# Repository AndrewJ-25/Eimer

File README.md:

# Eimer
Eimer is a wearable RP2040 devboard!

## Description and Features

A multi-axis accelerometer, 8 LEDs and 8 GPIO pads make Eimer an ideal wearable device. Solder pads are accompanied by holes to run the wire through, so there is no strain on the solder joint.

Eimer can be programmed using Arduino framework. Two mounting holes can be attached to a lanyard necklace, or safety pins.

Eimer can be powered with USB C or two CR2032 button cells (the board will work with one button cell, with a shorter battery life). Important note: do not plug in USB while cells are inserted!

I designed Eimer to get more comfortable with SMD and to learn more about MCUs. I started this project by following a tutorial posted in Hackclub Macondo before customising it.

The name comes from Irish mythology:)

## Assembly

All components can be soldered on a hotplate, except the coin cell holders which require hand-soldering.

## Schematic

## PCB

## BOM

|Designator                                                                              |Footprint                                  |Quantity|Description|Suggested source|Total cost, £|
|----------------------------------------------------------------------------------------|-------------------------------------------|--------|---------------------------|-----------|--|
|BT1, BT2                                                                                |BatteryHolder_Multicomp_BC-2001_1x2032     |2       |CR2032 cell holder|https://www.aliexpress.com/item/1005010097971513.html|2.00|
|C1, C10                                                                                 |0402                                       |2       |1uF capacitor|https://www.aliexpress.com/item/32435282135.html|0.67|
|C11, C12, C17, C2, C21, C3, C4, C5, C6, C7, C8, C9                                      |0402                                       |12      |0.1uF capacitor|https://www.aliexpress.com/item/32435282135.html|0.67
|C13, C14, C19, C20                                                                      |0603                                       |4       |10uF capacitor|https://www.aliexpress.com/item/1005007404529007.html|1.83|
|C15, C16                                                                                |0402                                       |2       |33pF capacitor|https://www.aliexpress.com/item/1005002960548572.html|1.27|
|D1, D2, D3, D4, D5, D6, D7, D8                                                          |0201                                       |8       |LED green|https://www.aliexpress.com/item/1005007406675682.html|5.05|
|J3                                                                                      |PinHeader_1x03_P2.54mm_Horizontal          |1       |1x3 horizontal pin header| https://www.aliexpress.com/item/1005007569841697.html|0.55|
|J4                                                                                      |USB_C_Receptacle_HRO_TYPE-C-31-M-12        |1       |USBC Receptacle|https://www.aliexpress.com/item/1005008805157100.html|1.04|
|L1                                                                                      |L_APV_ANR3015                              |1       |4.7uH inductor|https://www.aliexpress.com/item/1005001699576419.html|1.14|
|R1, R2                                                                                  |0402                                       |2       |5.1K resistor|https://www.aliexpress.com/item/4001321720241.html (multipack includes all required resistor values)|1.86|
|R10, R11, R12, R13, R14, R15, R16, R17, R5, R6                                          |0402                                       |10      |1k resistor|-|-|
|R18, R7                                                                                 |0402                                       |2       |10k resistor|-|-|
|R3, R4                                                                                  |0402                                       |2       |27ohm resistor|-|-|
|R8, R9                                                                                  |0402                                       |2       |4.7k resistor|-|-|
|RESET, RUN                                                                              |SW_Push_SPST_NO_Alps_SKRK                  |2       |Push switch|https://jlcpcb.com/partdetail/XUNPU-TS_1088AR02016/C720477|1.00|
|U1                                                                                      |QFN-56-1EP_7x7mm_P0.4mm_EP3.2x3.2mm        |1       |RP2040 MCU chip|https://www.aliexpress.com/item/1005007275652762.html|3.46|
|U2                                                                                      |SOT-23                                     |1       |MCP1700x-330xxTT voltage regulator|https://www.aliexpress.com/item/32808973510.html|0.99|
|U3                                                                                      |Texas_R-PDSO-G6                            |1       |TPS61221DCK boost converter|https://www.aliexpress.com/item/1005012857789997.html|3.69|
|U4                                                                                      |Winbond_USON-8-1EP_3x2mm_P0.5mm_EP0.2x1.6mm|1       |W25Q16JVUXIQ TR flash memory|https://www.aliexpress.com/item/1005012822339773.html|5.55|
|U5                                                                                      |LIS2DW12                                   |1       |LIS2DW12 accelerometer|https://www.aliexpress.com/item/1005009164629980.html|3.22|
|Y1                                                                                      |Crystal_SMD_3225-4Pin_3.2x2.5mm            |1       |12 MHz crystal|https://www.aliexpress.com/item/1005005409440787.html|2.50|
|PCB|-|1|PCB|https://jlcpcb.com/|2.95|
|Total| | | | |39.44|

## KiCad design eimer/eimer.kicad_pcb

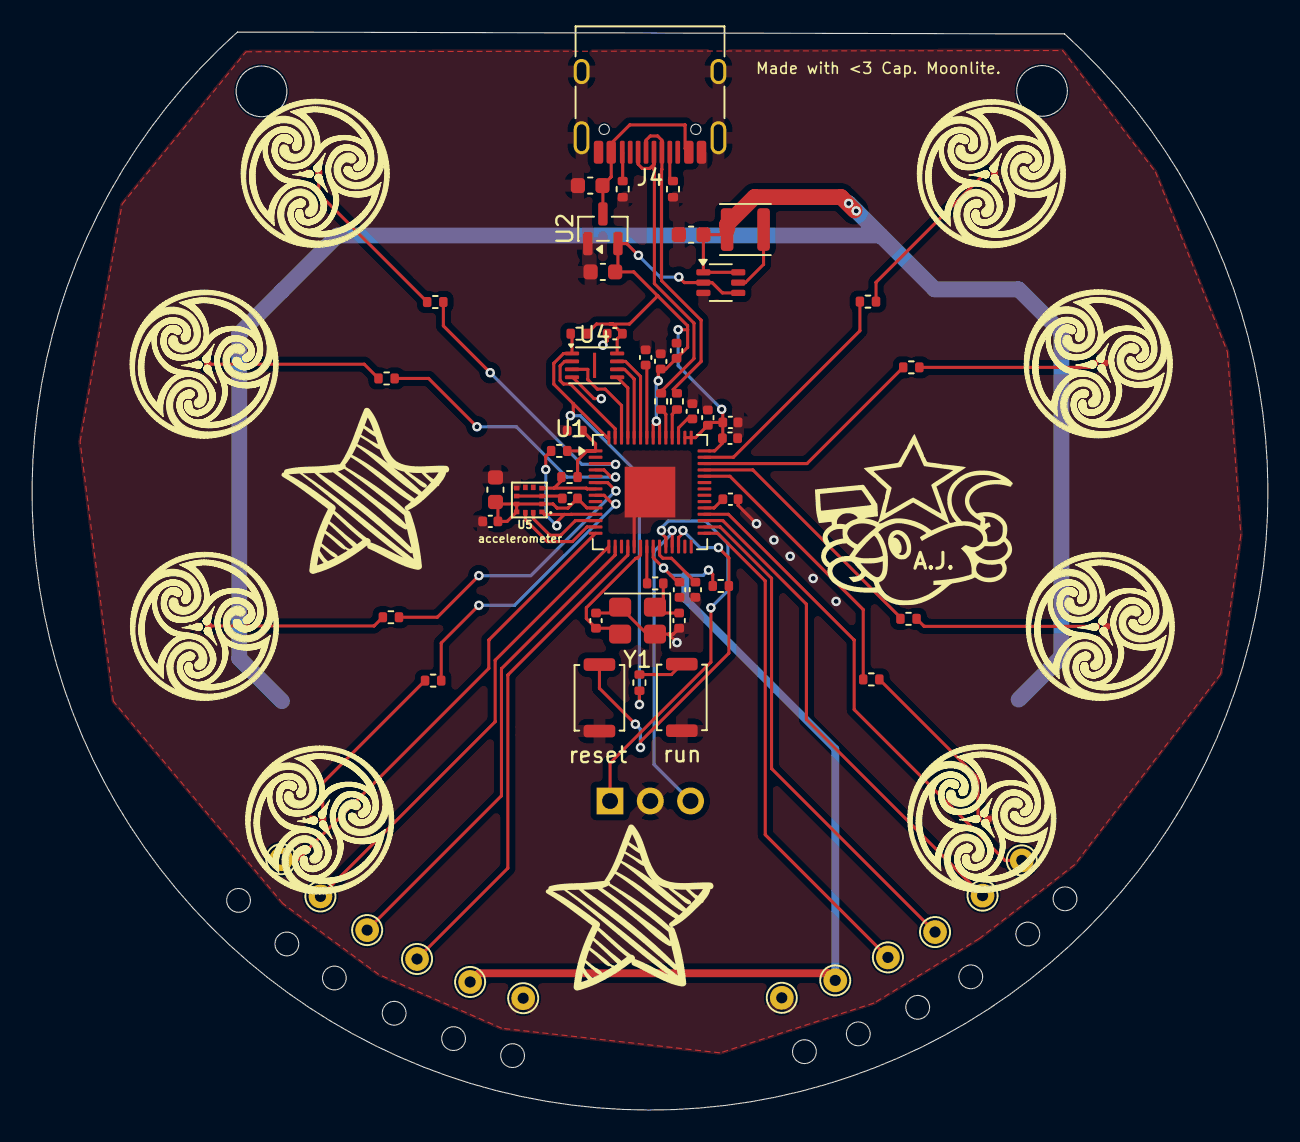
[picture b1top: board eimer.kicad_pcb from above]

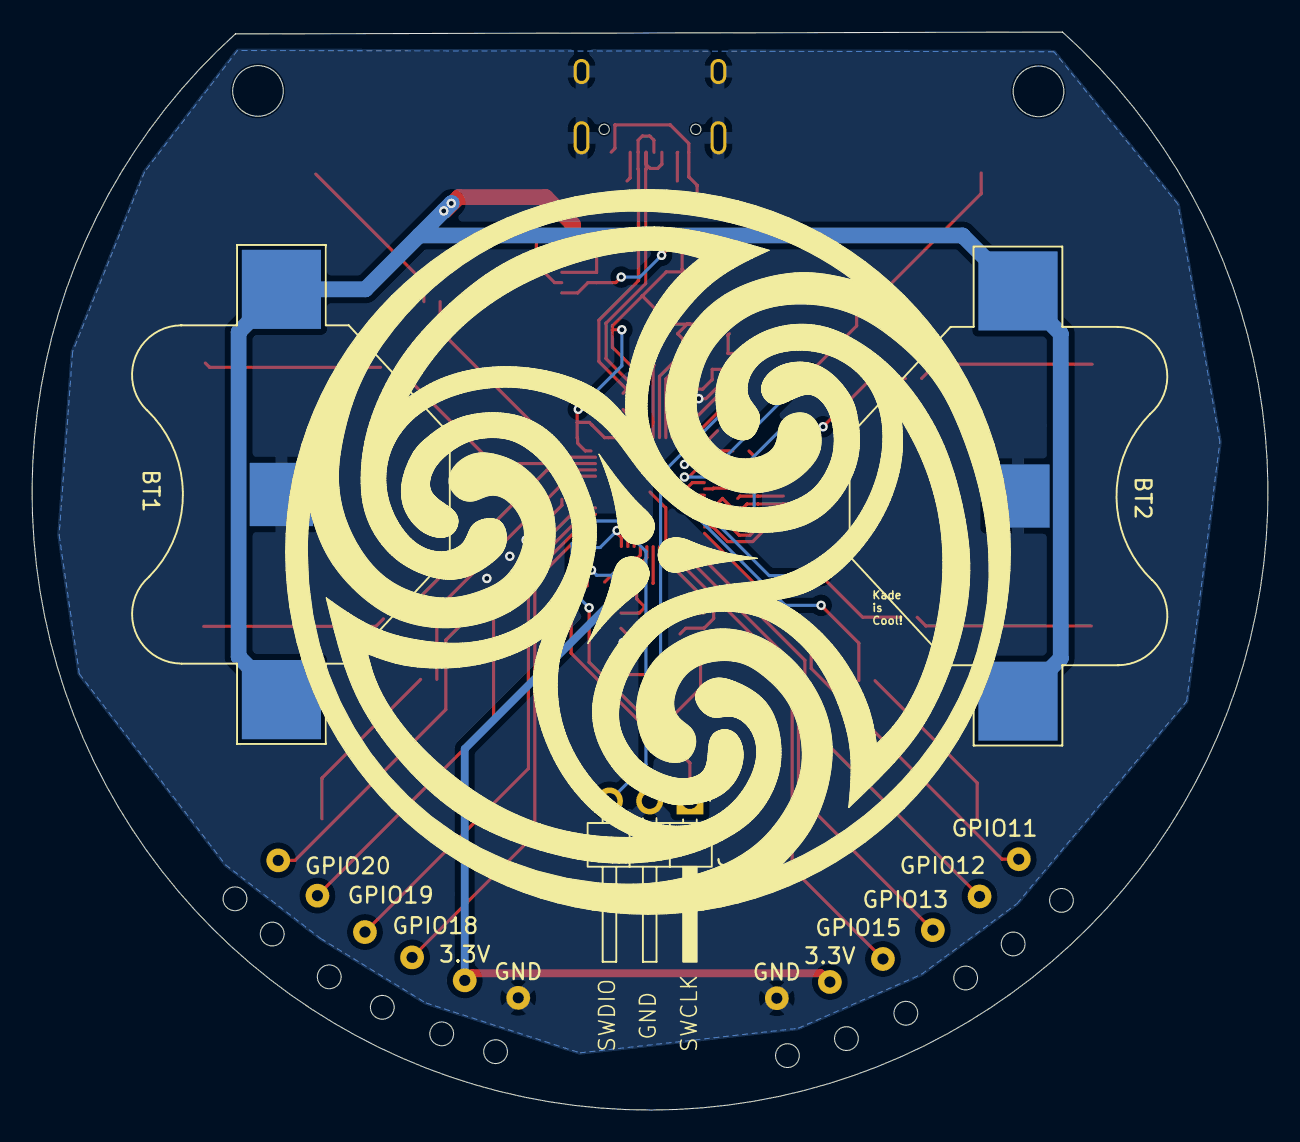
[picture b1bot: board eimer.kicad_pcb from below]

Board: 2 copper layers, 78.0 x 68.1 mm, 71 parts (3 on the bottom side), 53 nets.

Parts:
3.3V, 3.3V#2: TestPoint; TestPoint_THTPad_D1.5mm_Drill0.7mm
BT1, BT2: Battery_Cell; BatteryHolder_Multicomp_BC-2001_1x2032
C1, C10: 1uF; C_0402_1005Metric
C2, C3, C4, C5, C6, C7, C8, C9, C11, C12, C17, C21: 0.1uF; C_0402_1005Metric
C13, C14, C19, C20: 10uF; C_0603_1608Metric
C15, C16: 33pF; C_0402_1005Metric
D1, D2, D3, D4, D5, D6, D7, D8: LED; LED_0201_0603Metric
GND: TestPoint; TestPoint_THTPad_D1.5mm_Drill0.7mm
GND#2: TestPoint; TestPoint_THTPad_D1.5mm_Drill0.7mm
GPIO11, GPIO12, GPIO13, GPIO15, GPIO18, GPIO19, GPIO20, GPIO21: TestPoint; TestPoint_THTPad_D1.5mm_Drill0.7mm
J3: Conn_01x03; PinHeader_1x03_P2.54mm_Horizontal
J4: USB_C_Receptacle_USB2.0_14P; USB_C_Receptacle_HRO_TYPE-C-31-M-12
L1: 4.7uH; L_APV_ANR3015
R1, R2: 5.1K; R_0402_1005Metric
R3, R4: 27; R_0402_1005Metric
R5, R6: 1K; R_0402_1005Metric
R7: 10K; R_0402_1005Metric
R8, R9: 4.7k; R_0402_1005Metric
R10, R11, R12, R13, R14, R15, R16, R17: 1k; R_0402_1005Metric
R18: 10k; R_0402_1005Metric
U1: RP2040; QFN-56-1EP_7x7mm_P0.4mm_EP3.2x3.2mm
U2: MCP1700x-330xxTT; SOT-23
U3: TPS61221DCK; Texas_R-PDSO-G6
U4: W25Q16JVUXIQ TR; Winbond_USON-8-1EP_3x2mm_P0.5mm_EP0.2x1.6mm
U5: LIS2DW12; LIS2DS12
Y1: 12 MHz; Crystal_SMD_3225-4Pin_3.2x2.5mm
reset: SW_Push; SW_Push_SPST_NO_Alps_SKRK
run: SW_Push; SW_Push_SPST_NO_Alps_SKRK

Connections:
+1V1: C10.1, C11.1, C12.1, U1.23 (DVDD), U1.45 (VREG_VOUT), U1.50 (DVDD)
+3.3V: 3.3V.1 (1_1), 3.3V#2.1 (1_1), C1.1, C2.1, C3.1, C4.1, C5.1, C6.1, C7.1, C8.1, C9.1, C14.1, C17.1, C20.1, C21.1, R7.2, R8.1, R9.1, R18.1, U1.1 (IOVDD), U1.10 (IOVDD), U1.22 (IOVDD), U1.33 (IOVDD), U1.42 (IOVDD), U1.43 (ADC_AVDD), U1.44 (VREG_VIN), U1.48 (USB_VDD), U1.49 (IOVDD), U2.2 (VO), U3.2 (FB), U3.4 (VOUT), U4.8 (VCC), U5.2 (CS), U5.9 (VDD), U5.10 (VDD_IO)
GND: BT1.2 (-), BT2.2 (-), C1.2, C2.2, C3.2, C4.2, C5.2, C6.2, C7.2, C8.2, C9.2, C10.2, C11.2, C12.2, C13.2, C14.2, C15.1, C16.2, C17.2, C19.2, C20.2, C21.2, D1.1 (K), D2.1 (K), D3.1 (K), D4.1 (K), D5.1 (K), D6.1 (K), D7.1 (K), D8.1 (K), GND.1 (1_1), GND#2.1 (1_1), J3.2, J4.A1 (GND), J4.A12 (GND), J4.B1 (GND), J4.B12 (GND), J4.SH (SHIELD), R1.2, R2.1, U1.19 (TESTEN), U1.57 (GND), U2.1 (GND), U3.3 (GND), U4.4 (GND), U5.3 (SDO/SA0/MSDA), U5.6 (GND), U5.7 (RES), U5.8 (GND), Y1.2, Y1.4, reset.1, run.1
GPIO1: R10.2, U1.3 (GPIO1)
GPIO2: R11.2, U1.4 (GPIO2)
GPIO4: R12.2, U1.6 (GPIO4)
GPIO6: R13.2, U1.8 (GPIO6)
GPIO11: GPIO11.1 (1_1), U1.14 (GPIO11)
GPIO12: GPIO12.1 (1_1), U1.15 (GPIO12)
GPIO13: GPIO13.1 (1_1), U1.16 (GPIO13)
GPIO15: GPIO15.1 (1_1), U1.18 (GPIO15)
GPIO18: GPIO18.1 (1_1), U1.29 (GPIO18)
GPIO19: GPIO19.1 (1_1), U1.30 (GPIO19)
GPIO20: GPIO20.1 (1_1), U1.31 (GPIO20)
GPIO21: GPIO21.1 (1_1), U1.32 (GPIO21)
GPIO26/ADC0: R14.2, U1.38 (GPIO26/ADC0)
GPIO27/ADC1: R15.2, U1.39 (GPIO27/ADC1)
GPIO28/ADC2: R16.2, U1.40 (GPIO28/ADC2)
GPIO29/ADC3: R17.2, U1.41 (GPIO29/ADC3)
I2C_SCL: R8.2, U1.11 (GPIO8), U5.1 (SCL/SPC)
I2C_SDA: R9.2, U1.7 (GPIO5), U5.4 (SDA/SDI/SDO)
INT1: U1.12 (GPIO9), U5.12 (INT1)
INT2: U1.13 (GPIO10), U5.11 (INT2/MSCL)
unnamed: BT1.1 (+), BT2.1 (+), C19.1, L1.1, U3.1 (VIN), U3.6 (EN)
unnamed: C16.1, R5.1, Y1.1
unnamed: D1.2 (A), R10.1
unnamed: D2.2 (A), R11.1
unnamed: D3.2 (A), R12.1
unnamed: D4.2 (A), R13.1
unnamed: D5.2 (A), R14.1
unnamed: D6.2 (A), R15.1
unnamed: D7.2 (A), R16.1
unnamed: D8.2 (A), R17.1
unnamed: J4.A5 (CC1), R1.1
unnamed: J4.B5 (CC2), R2.2
unnamed: R6.1, run.2
unnamed: R18.2, U1.26 (RUN), reset.2
unnamed: R3.2, U1.46 (USB_DM)
unnamed: R4.1, U1.47 (USB_DP)
unnamed: L1.2, U3.5 (L)
QSPI_SCLK: U1.52 (QSPI_SCLK), U4.6 (CLK)
QSPI_SD0: U1.53 (QSPI_SD0), U4.5 (DI/IO_{0})
QSPI_SD1: U1.55 (QSPI_SD1), U4.2 (DO/IO_{1})
QSPI_SD2: U1.54 (QSPI_SD2), U4.3 (~WP/IO_{2})
QSPI_SD3: U1.51 (QSPI_SD3), U4.7 (~HOLD/~RESET/IO_{3})
QSPI_SS: R6.2, R7.1, U1.56 (~QSPI_SS), U4.1 (~CS)
SWCLK: J3.1, U1.24 (SWCLK)
SWDIO: J3.3, U1.25 (SWDIO)
USB_D+: J4.A6 (D+), J4.B6 (D+), R4.2
USB_D-: J4.A7 (D-), J4.B7 (D-), R3.1
VBUS: C13.1, J4.A4 (VBUS), J4.A9 (VBUS), J4.B4 (VBUS), J4.B9 (VBUS), U2.3 (VI)
XIN: C15.2, U1.20 (XIN), Y1.3
XOUT: R5.2, U1.21 (XOUT)

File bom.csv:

Designator,Footprint,Quantity,Value,LCSC Part #
"3.3V_2, 3.3V, GND_2, GND, GPIO11, GPIO12, GPIO13, GPIO15, GPIO18, GPIO19, GPIO20, GPIO21",TestPoint_THTPad_D1.5mm_Drill0.7mm,12,TestPoint,
"BT1, BT2",BatteryHolder_Multicomp_BC-2001_1x2032,2,Battery_Cell,
"C1, C10",0402,2,1uF,
"C11, C12, C17, C2, C21, C3, C4, C5, C6, C7, C8, C9",0402,12,0.1uF,
"C13, C14, C19, C20",0603,4,10uF,
"C15, C16",0402,2,33pF,
"D1, D2, D3, D4, D5, D6, D7, D8",0201,8,LED,
J3,PinHeader_1x03_P2.54mm_Horizontal,1,Conn_01x03,
J4,USB_C_Receptacle_HRO_TYPE-C-31-M-12,1,USB_C_Receptacle_USB2.0_14P,
L1,L_APV_ANR3015,1,4.7uH,
"R1, R2",0402,2,5.1K,
"R10, R11, R12, R13, R14, R15, R16, R17, R5, R6",0402,10,1k,
"R18, R7",0402,2,10k,
"R3, R4",0402,2,27,
"R8, R9",0402,2,4.7k,
"RESET, RUN",SW_Push_SPST_NO_Alps_SKRK,2,SW_Push,
U1,QFN-56-1EP_7x7mm_P0.4mm_EP3.2x3.2mm,1,RP2040,
U2,SOT-23,1,MCP1700x-330xxTT,
U3,Texas_R-PDSO-G6,1,TPS61221DCK,
U4,Winbond_USON-8-1EP_3x2mm_P0.5mm_EP0.2x1.6mm,1,W25Q16JVUXIQ TR,
U5,LIS2DS12,1,LIS2DW12,
Y1,Crystal_SMD_3225-4Pin_3.2x2.5mm,1,12 MHz,
